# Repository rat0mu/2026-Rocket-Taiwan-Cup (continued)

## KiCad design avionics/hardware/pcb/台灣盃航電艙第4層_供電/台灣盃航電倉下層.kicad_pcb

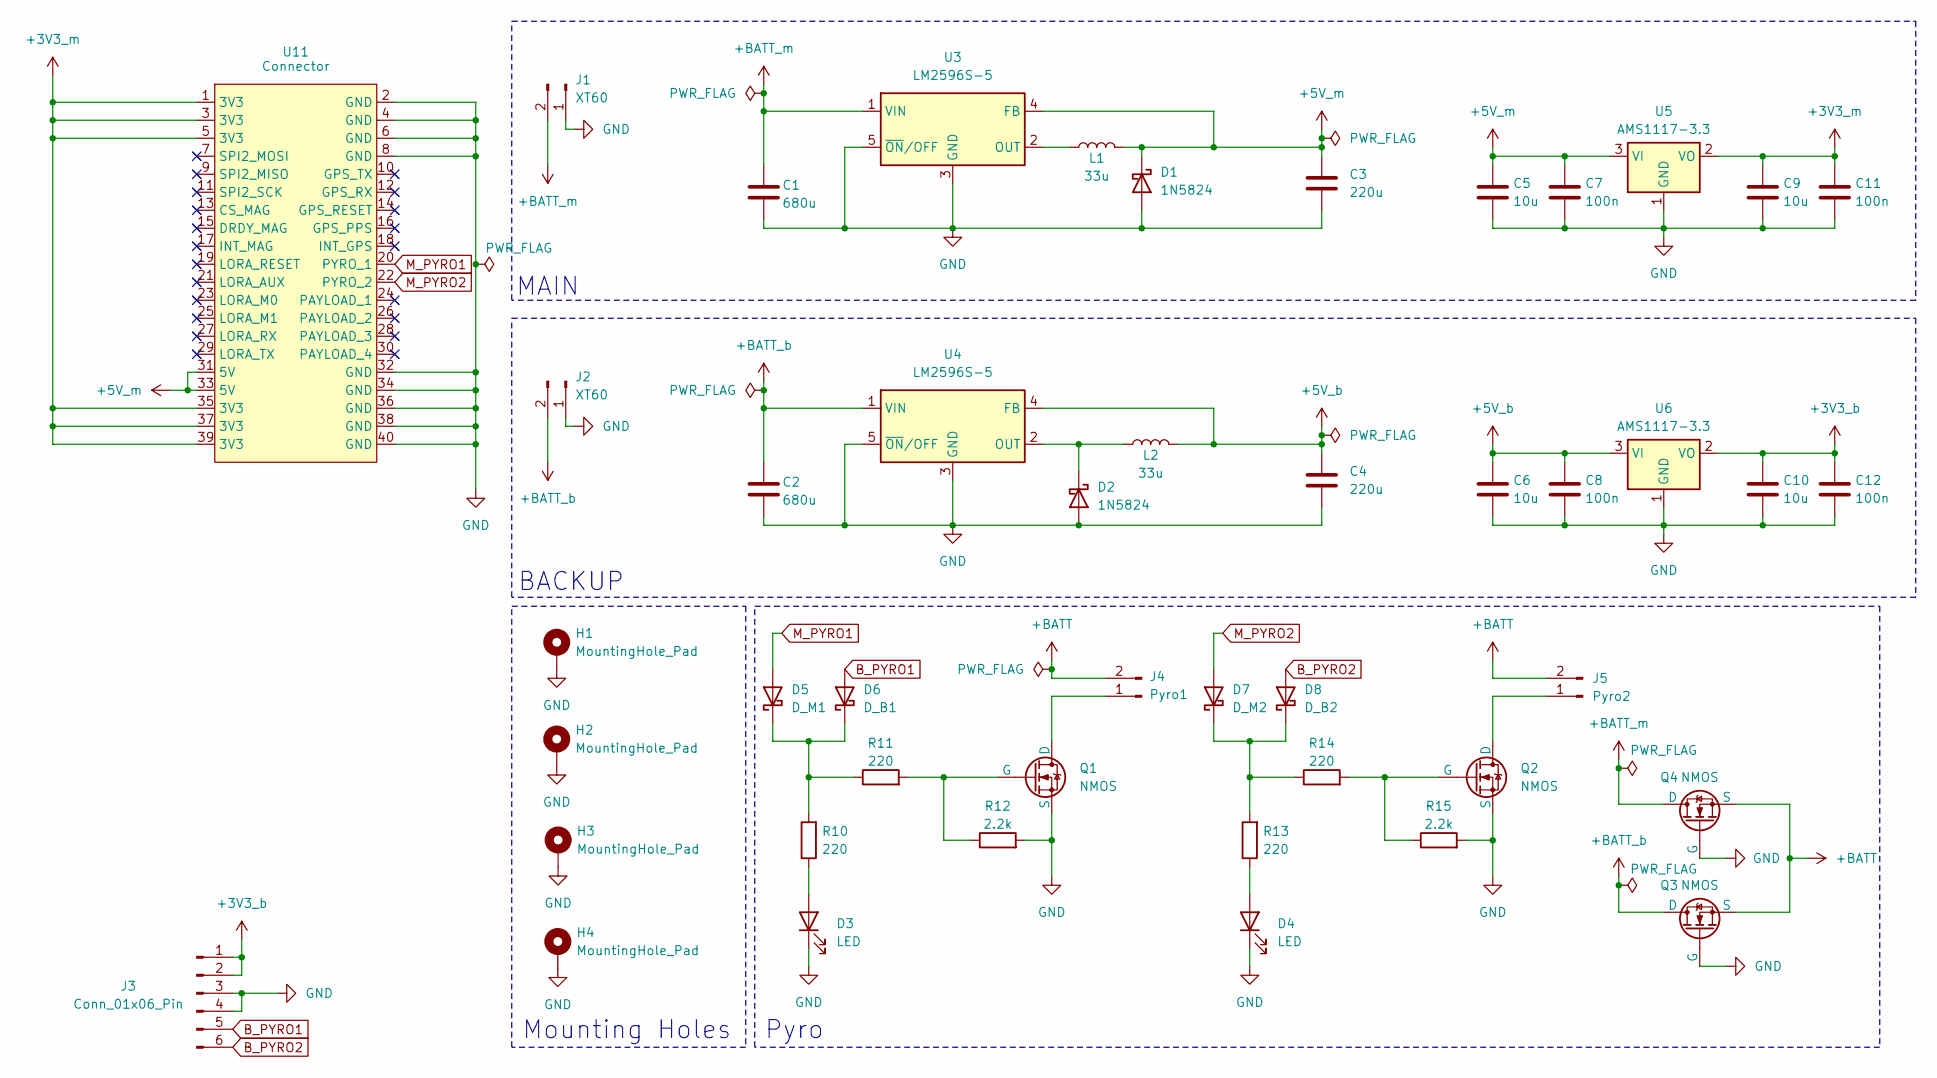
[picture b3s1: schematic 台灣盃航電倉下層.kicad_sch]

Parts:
C1, C2: 680u; CP_Elec_10x10
C3, C4: 220u; CP_Elec_8x10
C5, C6, C9, C10: 10u; C_0805_2012Metric
C7, C8, C11, C12: 100n; C_0603_1608Metric
D1, D2: 1N5824; D_SMC
D3, D4: LED; LED_0805_2012Metric
D5: D_M1; D_SOD-123
D6: D_B1; D_SOD-123
D7: D_M2; D_SOD-123
D8: D_B2; D_SOD-123
H1, H2, H3, H4: MountingHole_Pad; MountingHole_3.2mm_M3_ISO14580_Pad
J1, J2: XT60; AMASS_XT60PW-M_1x02_P7.20mm_Horizontal
J3: Conn_01x06_Pin; JST_XH_S6B-XH-A_1x06_P2.50mm_Horizontal
J4: Pyro1; JST_XH_S2B-XH-A_1x02_P2.50mm_Horizontal
J5: Pyro2; JST_XH_S2B-XH-A_1x02_P2.50mm_Horizontal
L1, L2: 33u; L_APV_ANR6045
Q1, Q2, Q3, Q4: NMOS; SOT-223
R10, R11, R13, R14: 220; R_0805_2012Metric
R12, R15: 2.2k; R_0805_2012Metric
U3, U4: LM2596S-5; TO-263-5_TabPin3
U5, U6: AMS1117-3.3; SOT-223-3_TabPin2
U11: Connector; PinHeader_2x20_P2.54mm_Vertical

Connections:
+3V3_b: C10.1, C12.1, J3.1, J3.2, U6.2 (VO)
+3V3_m: C9.1, C11.1, U5.2 (VO), U11.1 (3V3), U11.3 (3V3), U11.5 (3V3), U11.35 (3V3), U11.37 (3V3), U11.39 (3V3)
+5V_b: C4.1, C6.1, C8.1, L2.2, U4.4 (FB), U6.3 (VI)
+5V_m: C3.1, C5.1, C7.1, D1.1 (K), L1.2, U3.4 (FB), U5.3 (VI), U11.31 (5V), U11.33 (5V)
+BATT: J4.2, J5.2, Q3.3 (S), Q4.3 (S); also elsewhere on the board
+BATT_b: C2.1, J2.2, Q3.1 (D), U4.1 (VIN)
+BATT_m: C1.1, J1.2, Q4.1 (D), U3.1 (VIN)
B_PYRO1: D6.2 (A), J3.5
B_PYRO2: D8.2 (A), J3.6
GND: C1.2, C2.2, C3.2, C4.2, C5.2, C6.2, C7.2, C8.2, C9.2, C10.2, C11.2, C12.2, D1.2 (A), D2.2 (A), D3.1 (K), D4.1 (K), H1.1, H2.1, H3.1, H4.1, J1.1, J2.1, J3.3, J3.4, Q1.3 (S), Q2.3 (S), Q3.2 (G), Q4.2 (G), R12.2, R15.2, U3.3 (GND), U3.5 (~ON/OFF), U4.3 (GND), U4.5 (~ON/OFF), U5.1 (GND), U6.1 (GND), U11.2 (GND), U11.4 (GND), U11.6 (GND), U11.8 (GND), U11.32 (GND), U11.34 (GND), U11.36 (GND), U11.38 (GND), U11.40 (GND)
M_PYRO1: D5.2 (A), U11.20 (PYRO_1)
M_PYRO2: D7.2 (A), U11.22 (PYRO_2)
unnamed: D2.1 (K), L2.1, U4.2 (OUT)
unnamed: D3.2 (A), R10.1
unnamed: D4.2 (A), R13.1
unnamed: D5.1 (K), D6.1 (K), R10.2, R11.1
unnamed: D7.1 (K), D8.1 (K), R13.2, R14.1
unnamed 17: J4.1, Q1.1 (D); also elsewhere on the board
unnamed 18: J5.1, Q2.1 (D); also elsewhere on the board
unnamed: Q1.2 (G), R11.2, R12.1
unnamed: Q2.2 (G), R14.2, R15.1
unnamed: L1.1, U3.2 (OUT)

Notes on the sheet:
MAIN
Pyro
BACKUP
Mounting Holes

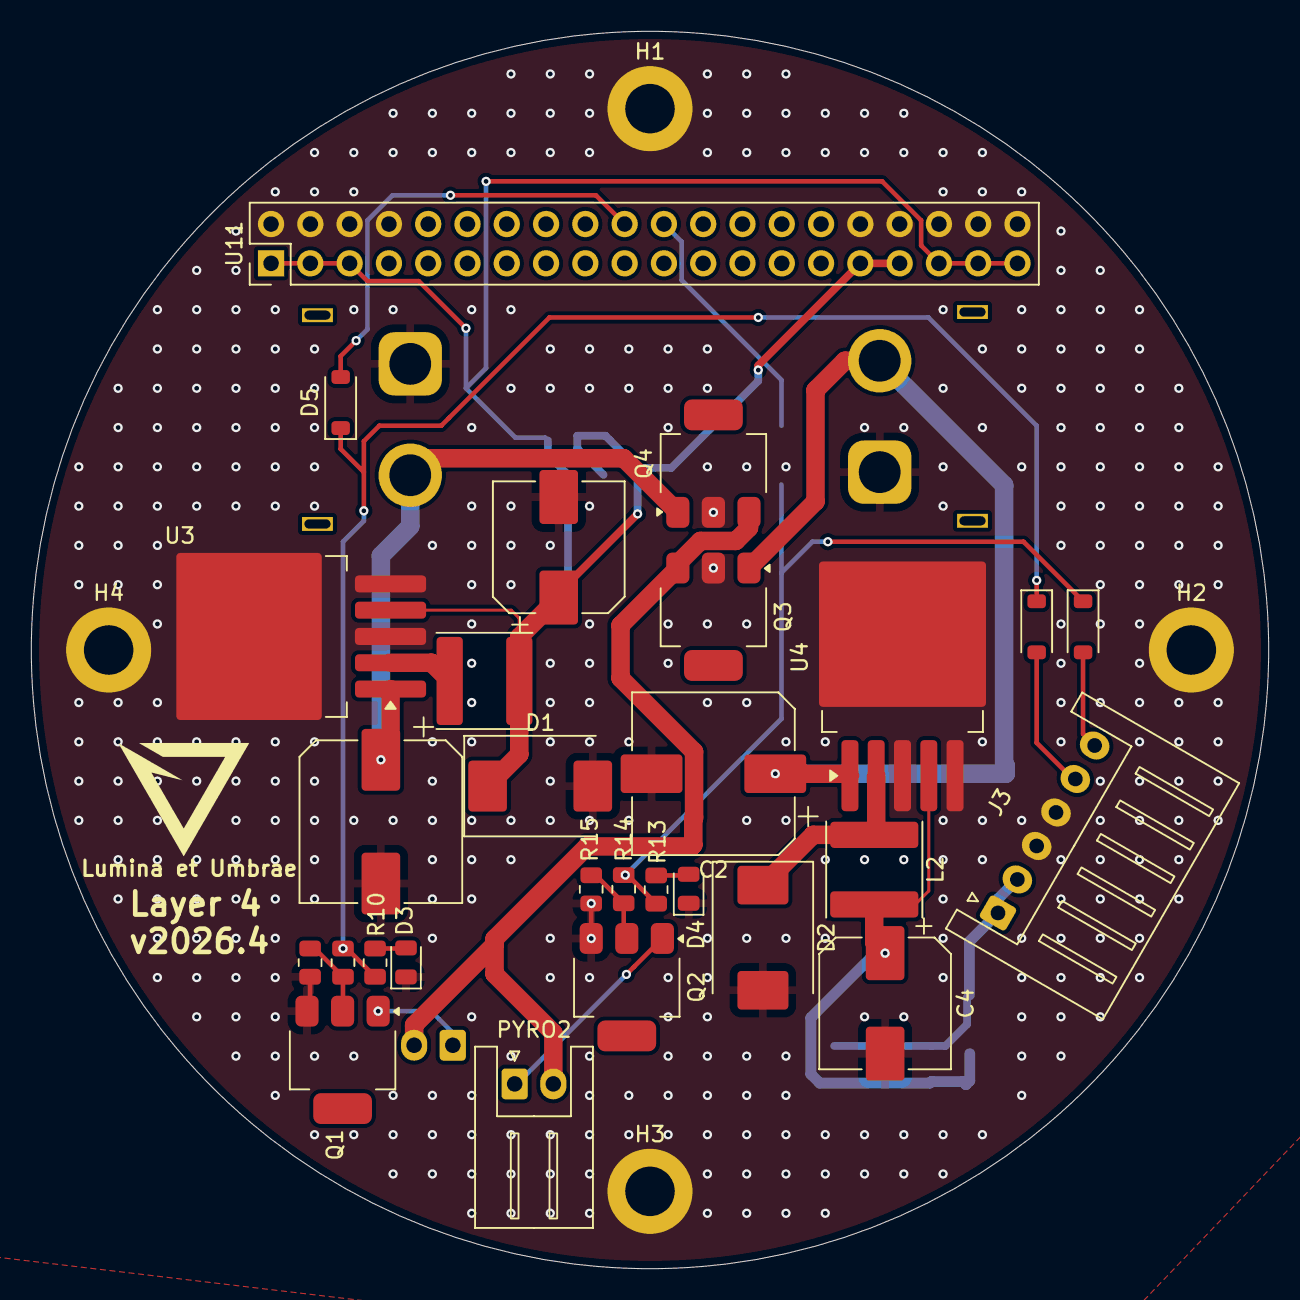
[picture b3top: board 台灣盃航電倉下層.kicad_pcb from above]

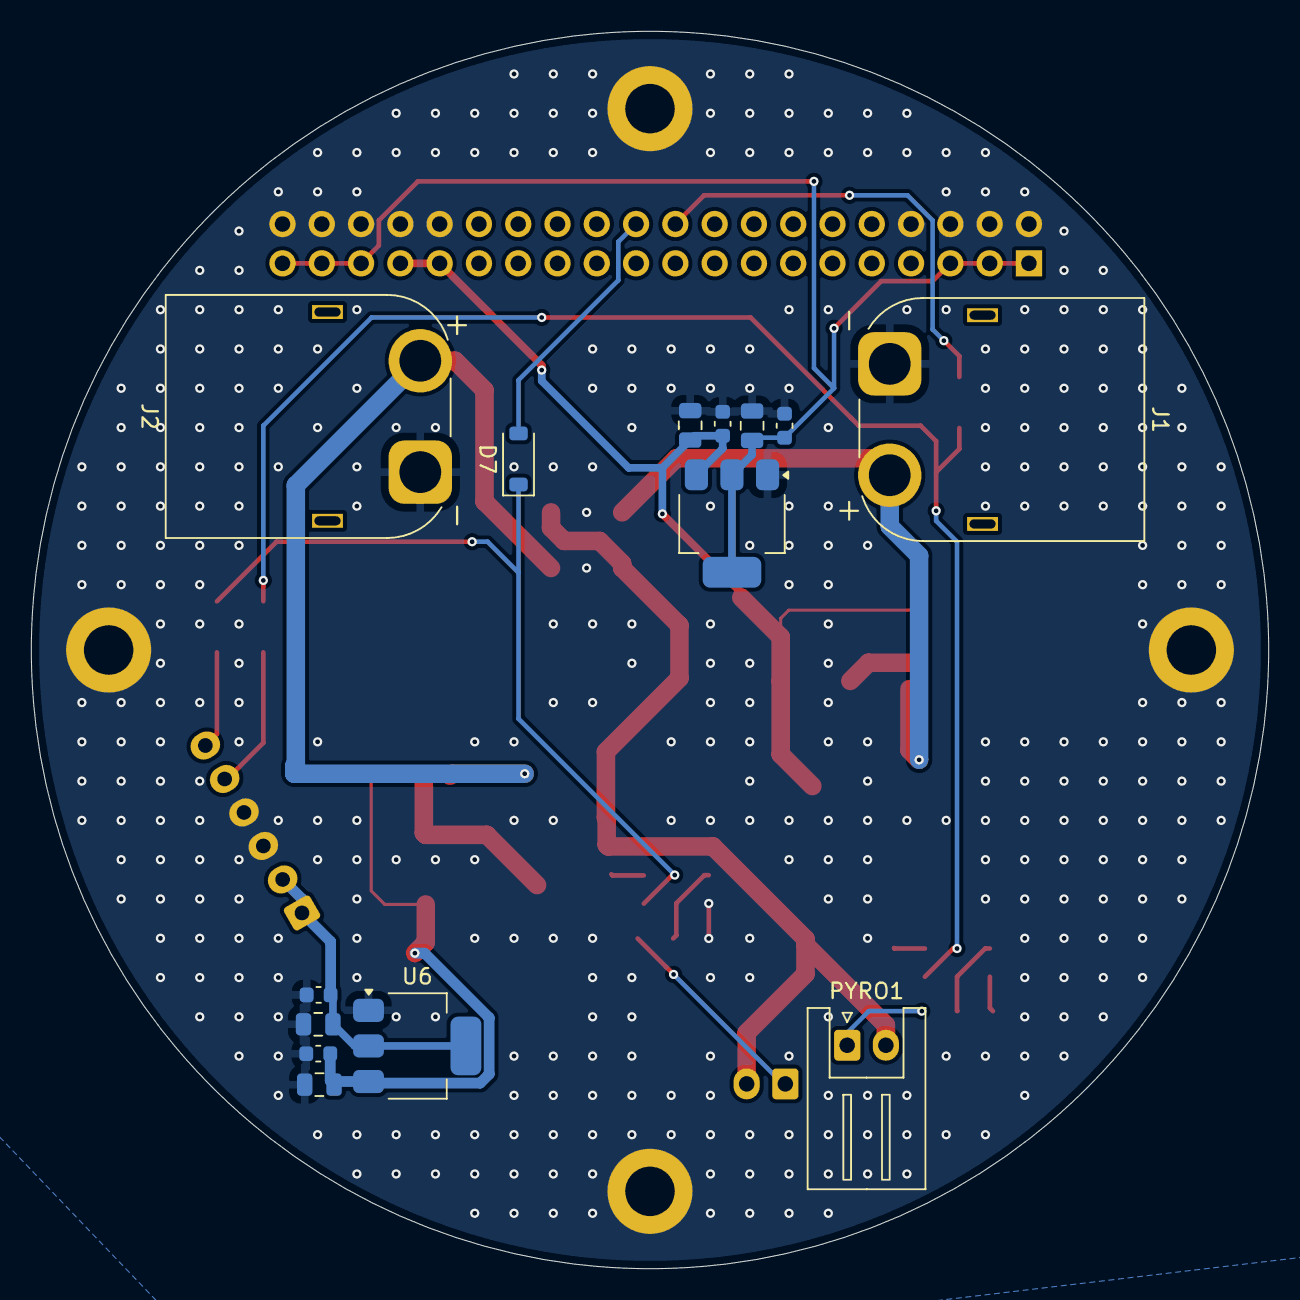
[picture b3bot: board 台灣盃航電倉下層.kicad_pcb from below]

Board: 2 copper layers, 80.0 x 80.0 mm, 46 parts (14 on the bottom side), 22 nets.

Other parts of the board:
PYRO1: Pyro1; JST_XH_S2B-XH-A_1x02_P2.50mm_Horizontal
PYRO2: Pyro2; JST_XH_S2B-XH-A_1x02_P2.50mm_Horizontal

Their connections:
+BATT: PYRO1.2, PYRO2.2; also elsewhere on the board
unnamed 17: PYRO1.1; also elsewhere on the board
unnamed 18: PYRO2.1; also elsewhere on the board

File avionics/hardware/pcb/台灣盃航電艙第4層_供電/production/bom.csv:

Designator,Footprint,Quantity,Value,LCSC Part #
"C1, C2",CP_Elec_10x10,2,680u,
"C10, C5, C6, C9",0805,4,10u,
"C11, C12, C7, C8",0603,4,100n,
"C3, C4",CP_Elec_8x10,2,220u,
"D1, D2",D_SMC,2,1N5824,
"D3, D4",0805,2,LED,
D5,D_SOD-123,1,D_M1,
D6,D_SOD-123,1,D_B1,
D7,D_SOD-123,1,D_M2,
D8,D_SOD-123,1,D_B2,
"J1, J2",AMASS_XT60PW-M_1x02_P7.20mm_Horizontal,2,XT60,
J3,JST_XH_S6B-XH-A_1x06_P2.50mm_Horizontal,1,Conn_01x06_Pin,
"L1, L2",L_APV_ANR6045,2,33u,
PYRO1,JST_XH_S2B-XH-A_1x02_P2.50mm_Horizontal,1,Pyro1,
PYRO2,JST_XH_S2B-XH-A_1x02_P2.50mm_Horizontal,1,Pyro2,
"Q1, Q2, Q3, Q4",SOT-223,4,NMOS,
"R10, R11, R13, R14",0805,4,220,
"R12, R15",0805,2,2.2k,
U11,PinHeader_2x20_P2.54mm_Vertical,1,Connector,
"U3, U4",TO-263-5_TabPin3,2,LM2596S-5,
"U5, U6",SOT-223-3_TabPin2,2,AMS1117-3.3,

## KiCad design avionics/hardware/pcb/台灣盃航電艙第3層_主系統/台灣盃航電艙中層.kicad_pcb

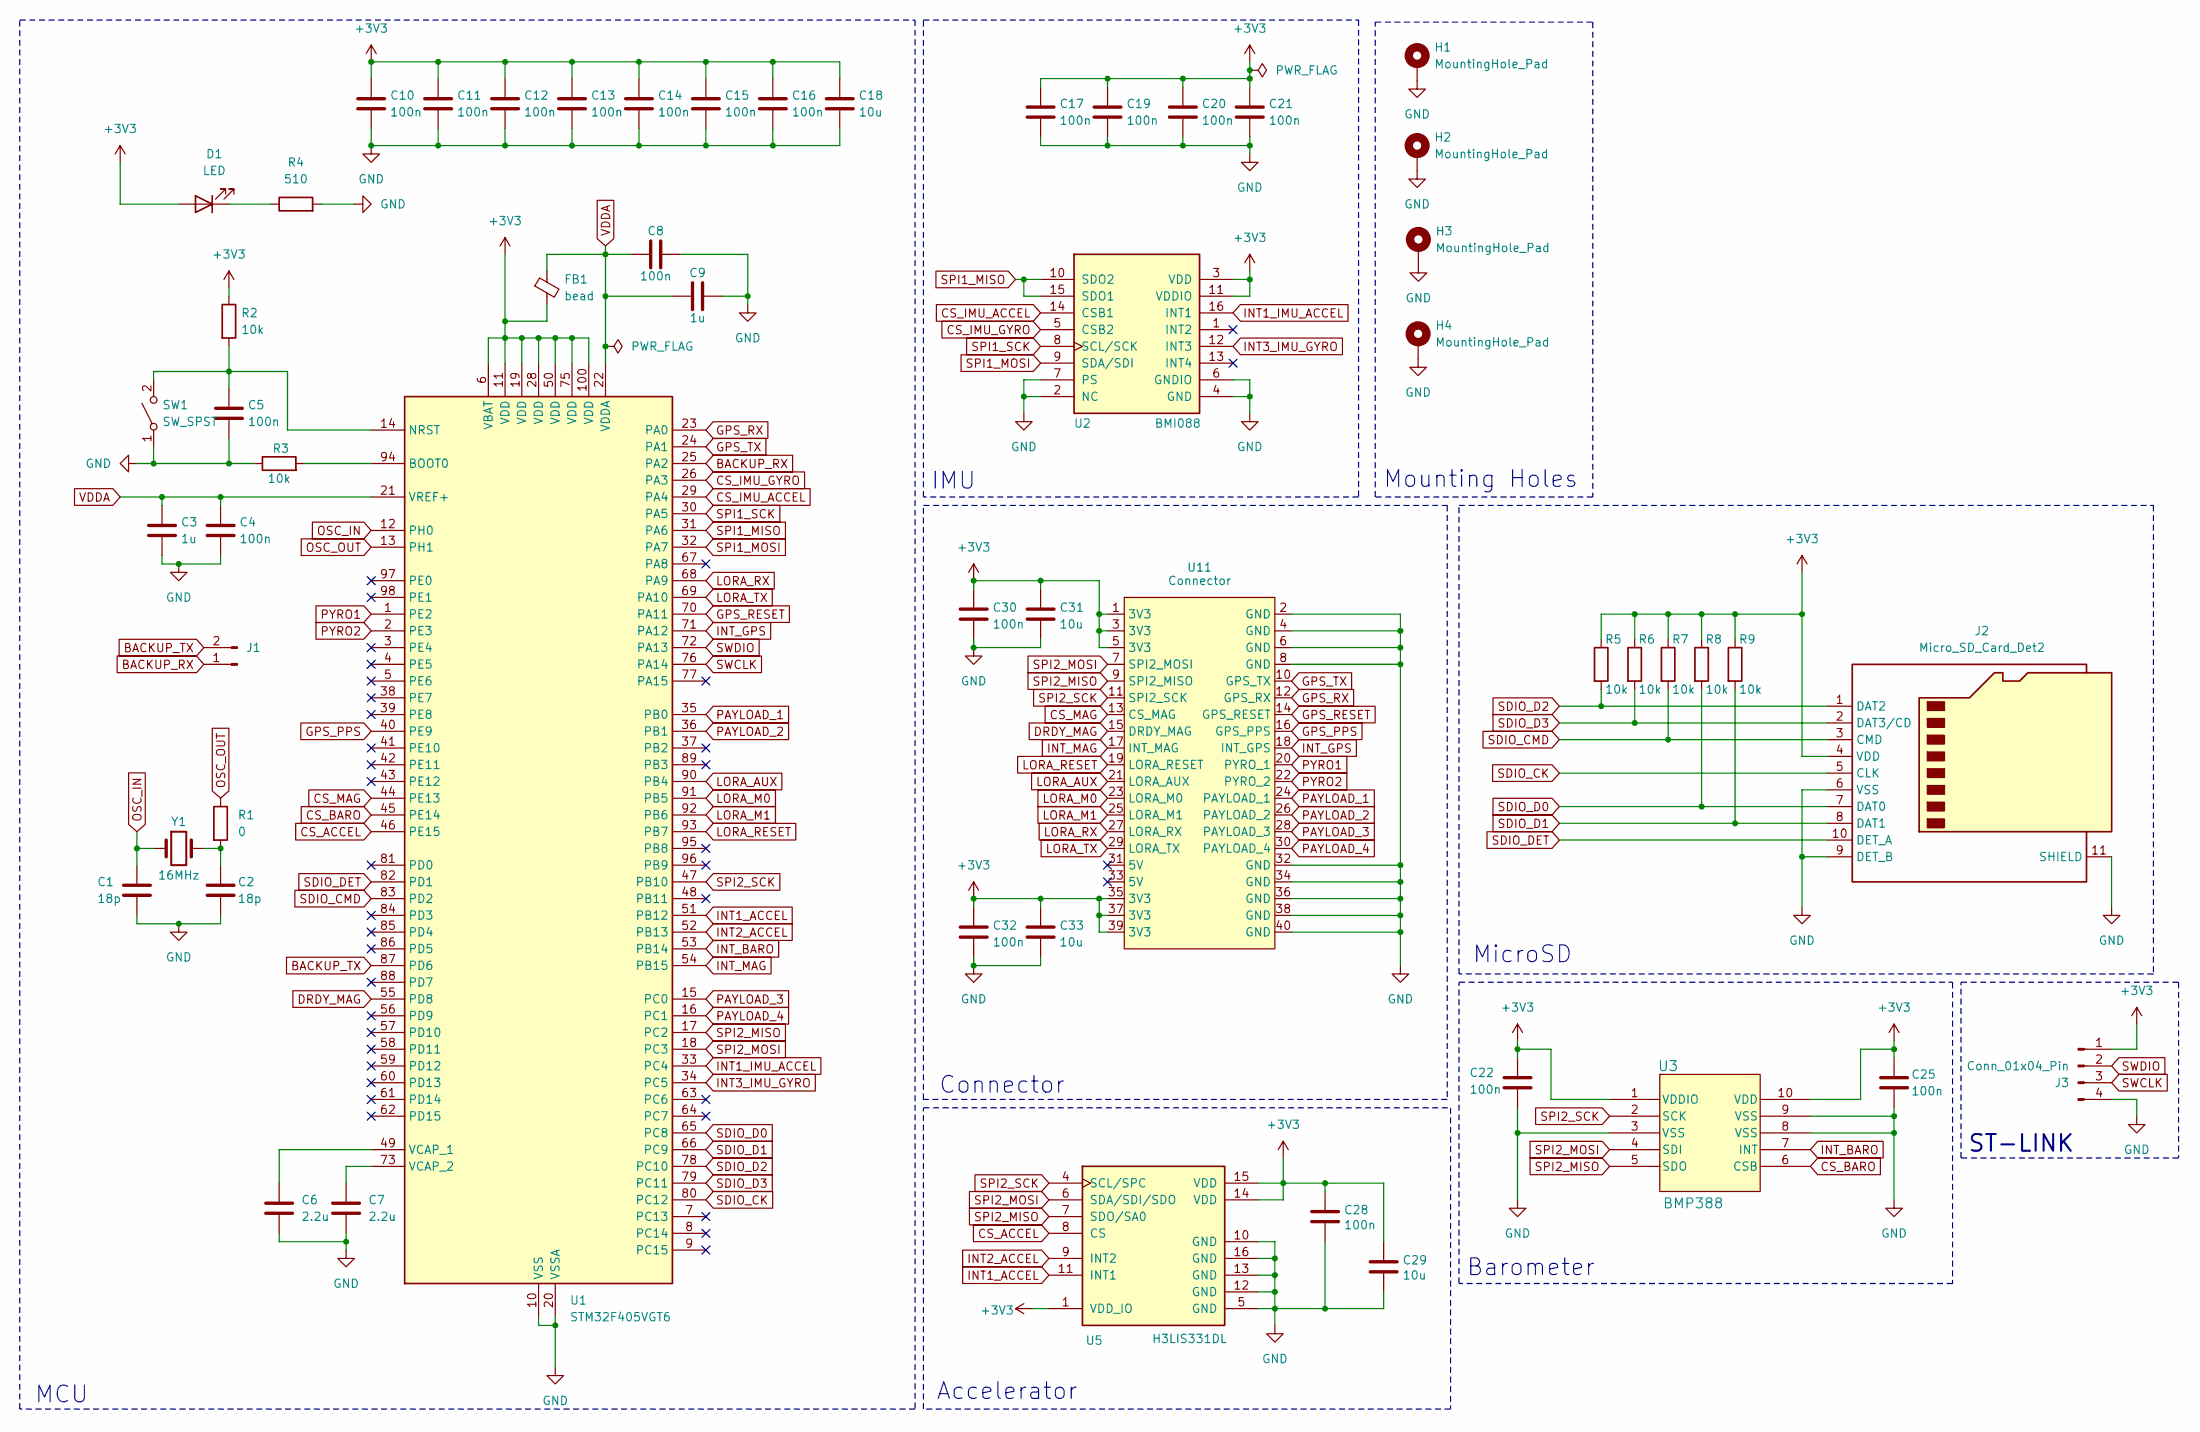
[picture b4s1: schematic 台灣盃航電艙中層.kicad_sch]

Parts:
C1, C2: 18p; C_0603_1608Metric
C3, C9: 1u; C_0603_1608Metric
C4, C5, C8, C10, C11, C12, C13, C14, C15, C16, C17, C19, C20, C21, C22, C25, C28: 100n; C_0603_1608Metric
C6, C7: 2.2u; C_0805_2012Metric
C18, C29: 10u; C_0805_2012Metric
C30, C32: 100n; C_0402_1005Metric
C31, C33: 10u; C_0603_1608Metric
D1: LED; LED_0805_2012Metric
FB1: bead; L_0603_1608Metric
H1, H2, H3, H4: MountingHole_Pad; MountingHole_3.2mm_M3_ISO14580_Pad
J1: JST_XH_S2B-XH-A_1x02_P2.50mm_Horizontal
J2: Micro_SD_Card_Det2; microSD_HC_Hirose_DM3D-SF
J3: Conn_01x04_Pin; PinHeader_1x04_P2.54mm_Horizontal
R1: 0; R_0603_1608Metric
R2, R5, R6, R7, R8, R9: 10k; R_0603_1608Metric
R3: 10k; C_0603_1608Metric
R4: 510; R_0805_2012Metric
SW1: SW_SPST; SW_SPST_FSMSM
U1: STM32F405VGT6; LQFP-100_14x14mm_P0.5mm
U2: BMI088; PQFN50P450X300X100-16N
U3: BMP388; XDCR_BMP390L
U5: H3LIS331DL; QFN300X300X100-16N
U11: Connector; PinHeader_2x20_P2.54mm_Vertical
Y1: 16MHz; Crystal_SMD_3225-4Pin_3.2x2.5mm

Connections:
+3V3: C10.1, C11.1, C12.1, C13.1, C14.1, C15.1, C16.1, C17.1, C18.1, C19.1, C20.1, C21.1, C22.1, C25.1, C28.1, C29.1, C30.1, C31.1, C32.1, C33.1, D1.2 (A), FB1.2, J2.4 (VDD), J3.1, R2.1, R5.1, R6.1, R7.1, R8.1, R9.1, U1.6 (VBAT), U1.11 (VDD), U1.19 (VDD), U1.28 (VDD), U1.50 (VDD), U1.75 (VDD), U1.100 (VDD), U2.3 (VDD), U2.11 (VDDIO), U3.1 (VDDIO), U3.10 (VDD), U5.1 (VDD_IO), U5.14 (VDD), U5.15 (VDD), U11.1 (3V3), U11.3 (3V3), U11.5 (3V3), U11.35 (3V3), U11.37 (3V3), U11.39 (3V3)
BACKUP_RX: J1.1, U1.25 (PA2)
BACKUP_TX: J1.2, U1.87 (PD6)
CS_ACCEL: U1.46 (PE15), U5.8 (CS)
CS_BARO: U1.45 (PE14), U3.6 (CSB)
CS_IMU_ACCEL: U1.29 (PA4), U2.14 (CSB1)
CS_IMU_GYRO: U1.26 (PA3), U2.5 (CSB2)
CS_MAG: U1.44 (PE13), U11.13 (CS_MAG)
DRDY_MAG: U1.55 (PD8), U11.15 (DRDY_MAG)
GND: C1.2, C2.2, C3.2, C4.2, C5.2, C6.2, C7.2, C8.1, C9.2, C10.2, C11.2, C12.2, C13.2, C14.2, C15.2, C16.2, C17.2, C18.2, C19.2, C20.2, C21.2, C22.2, C25.2, C28.2, C29.2, C30.2, C31.2, C32.2, C33.2, H1.1, H2.1, H3.1, H4.1, J2.6 (VSS), J2.9 (DET_B), J2.11 (SHIELD), J3.4, R3.1, R4.2, SW1.1 (A), U1.10 (VSS), U1.20 (VSSA), U1.27 (VSS), U1.74 (VSS), U1.99 (VSS), U2.2 (NC), U2.4 (GND), U2.6 (GNDIO), U2.7 (PS), U3.3 (VSS), U3.8 (VSS), U3.9 (VSS), U5.5 (GND), U5.10 (GND), U5.12 (GND), U5.13 (GND), U5.16 (GND), U11.2 (GND), U11.4 (GND), U11.6 (GND), U11.8 (GND), U11.32 (GND), U11.34 (GND), U11.36 (GND), U11.38 (GND), U11.40 (GND)
GPS_PPS: U1.40 (PE9), U11.16 (GPS_PPS)
GPS_RESET: U1.70 (PA11), U11.14 (GPS_RESET)
GPS_RX: U1.23 (PA0), U11.12 (GPS_RX)
GPS_TX: U1.24 (PA1), U11.10 (GPS_TX)
INT1_ACCEL: U1.51 (PB12), U5.11 (INT1)
INT1_IMU_ACCEL: U1.33 (PC4), U2.16 (INT1)
INT2_ACCEL: U1.52 (PB13), U5.9 (INT2)
INT3_IMU_GYRO: U1.34 (PC5), U2.12 (INT3)
INT_BARO: U1.53 (PB14), U3.7 (INT)
INT_GPS: U1.71 (PA12), U11.18 (INT_GPS)
INT_MAG: U1.54 (PB15), U11.17 (INT_MAG)
LORA_AUX: U1.90 (PB4), U11.21 (LORA_AUX)
LORA_M0: U1.91 (PB5), U11.23 (LORA_M0)
LORA_M1: U1.92 (PB6), U11.25 (LORA_M1)
LORA_RESET: U1.93 (PB7), U11.19 (LORA_RESET)
LORA_RX: U1.68 (PA9), U11.27 (LORA_RX)
LORA_TX: U1.69 (PA10), U11.29 (LORA_TX)
unnamed: C2.1, R1.2, Y1.2
unnamed: D1.1 (K), R4.1
unnamed: C5.1, R2.2, SW1.2 (B), U1.14 (NRST)
unnamed: R3.2, U1.94 (BOOT0)
unnamed: C6.1, U1.49 (VCAP_1)
unnamed: C7.1, U1.73 (VCAP_2)
OSC_IN: C1.1, U1.12 (PH0), Y1.1
OSC_OUT: R1.1, U1.13 (PH1)
PAYLOAD_1: U1.35 (PB0), U11.24 (PAYLOAD_1)
PAYLOAD_2: U1.36 (PB1), U11.26 (PAYLOAD_2)
PAYLOAD_3: U1.15 (PC0), U11.28 (PAYLOAD_3)
PAYLOAD_4: U1.16 (PC1), U11.30 (PAYLOAD_4)
PYRO1: U1.1 (PE2), U11.20 (PYRO_1)
PYRO2: U1.2 (PE3), U11.22 (PYRO_2)
SDIO_CK: J2.5 (CLK), U1.80 (PC12)
SDIO_CMD: J2.3 (CMD), R7.2, U1.83 (PD2)
SDIO_D0: J2.7 (DAT0), R8.2, U1.65 (PC8)
SDIO_D1: J2.8 (DAT1), R9.2, U1.66 (PC9)
SDIO_D2: J2.1 (DAT2), R5.2, U1.78 (PC10)
SDIO_D3: J2.2 (DAT3/CD), R6.2, U1.79 (PC11)
SDIO_DET: J2.10 (DET_A), U1.82 (PD1)
SPI1_MISO: U1.31 (PA6), U2.10 (SDO2), U2.15 (SDO1)
SPI1_MOSI: U1.32 (PA7), U2.9 (SDA/SDI)
SPI1_SCK: U1.30 (PA5), U2.8 (SCL/SCK)
SPI2_MISO: U1.17 (PC2), U3.5 (SDO), U5.7 (SDO/SA0), U11.9 (SPI2_MISO)
SPI2_MOSI: U1.18 (PC3), U3.4 (SDI), U5.6 (SDA/SDI/SDO), U11.7 (SPI2_MOSI)
SPI2_SCK: U1.47 (PB10), U3.2 (SCK), U5.4 (SCL/SPC), U11.11 (SPI2_SCK)
SWCLK: J3.3, U1.76 (PA14)
SWDIO: J3.2, U1.72 (PA13)
VDDA: C3.1, C4.1, C8.2, C9.1, FB1.1, U1.21 (VREF+), U1.22 (VDDA)

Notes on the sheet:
IMU
MCU
Mounting Holes
Accelerator
MicroSD
Connector
ST-LINK
Barometer

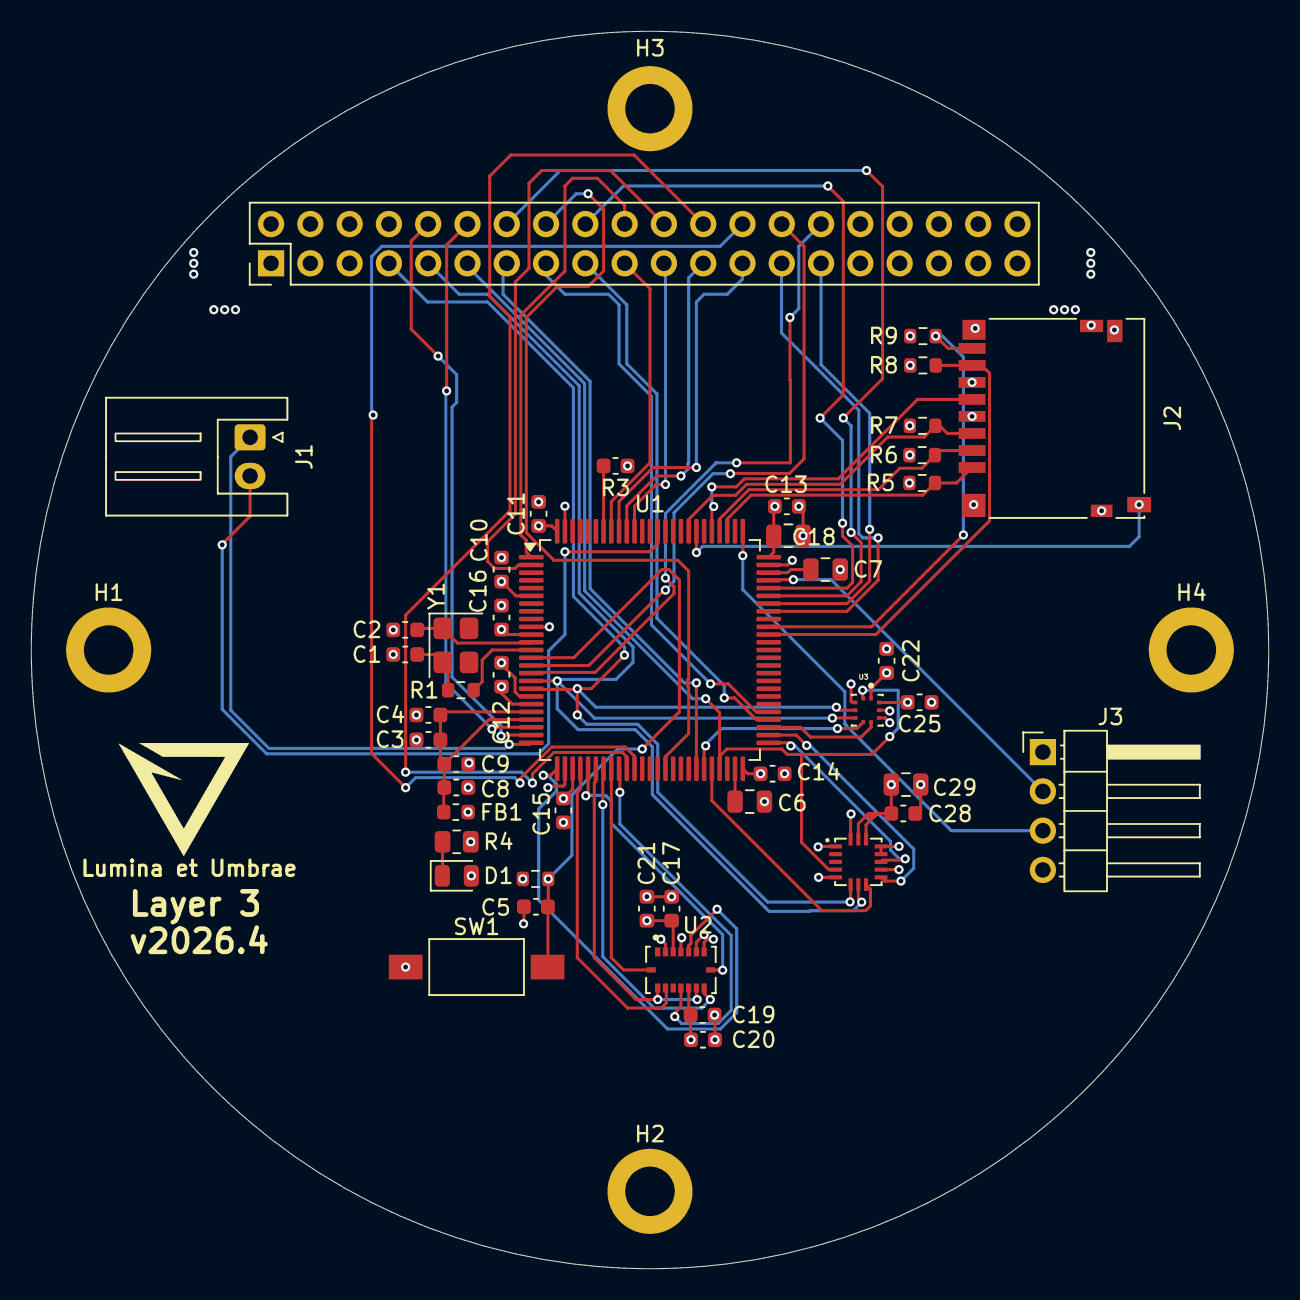
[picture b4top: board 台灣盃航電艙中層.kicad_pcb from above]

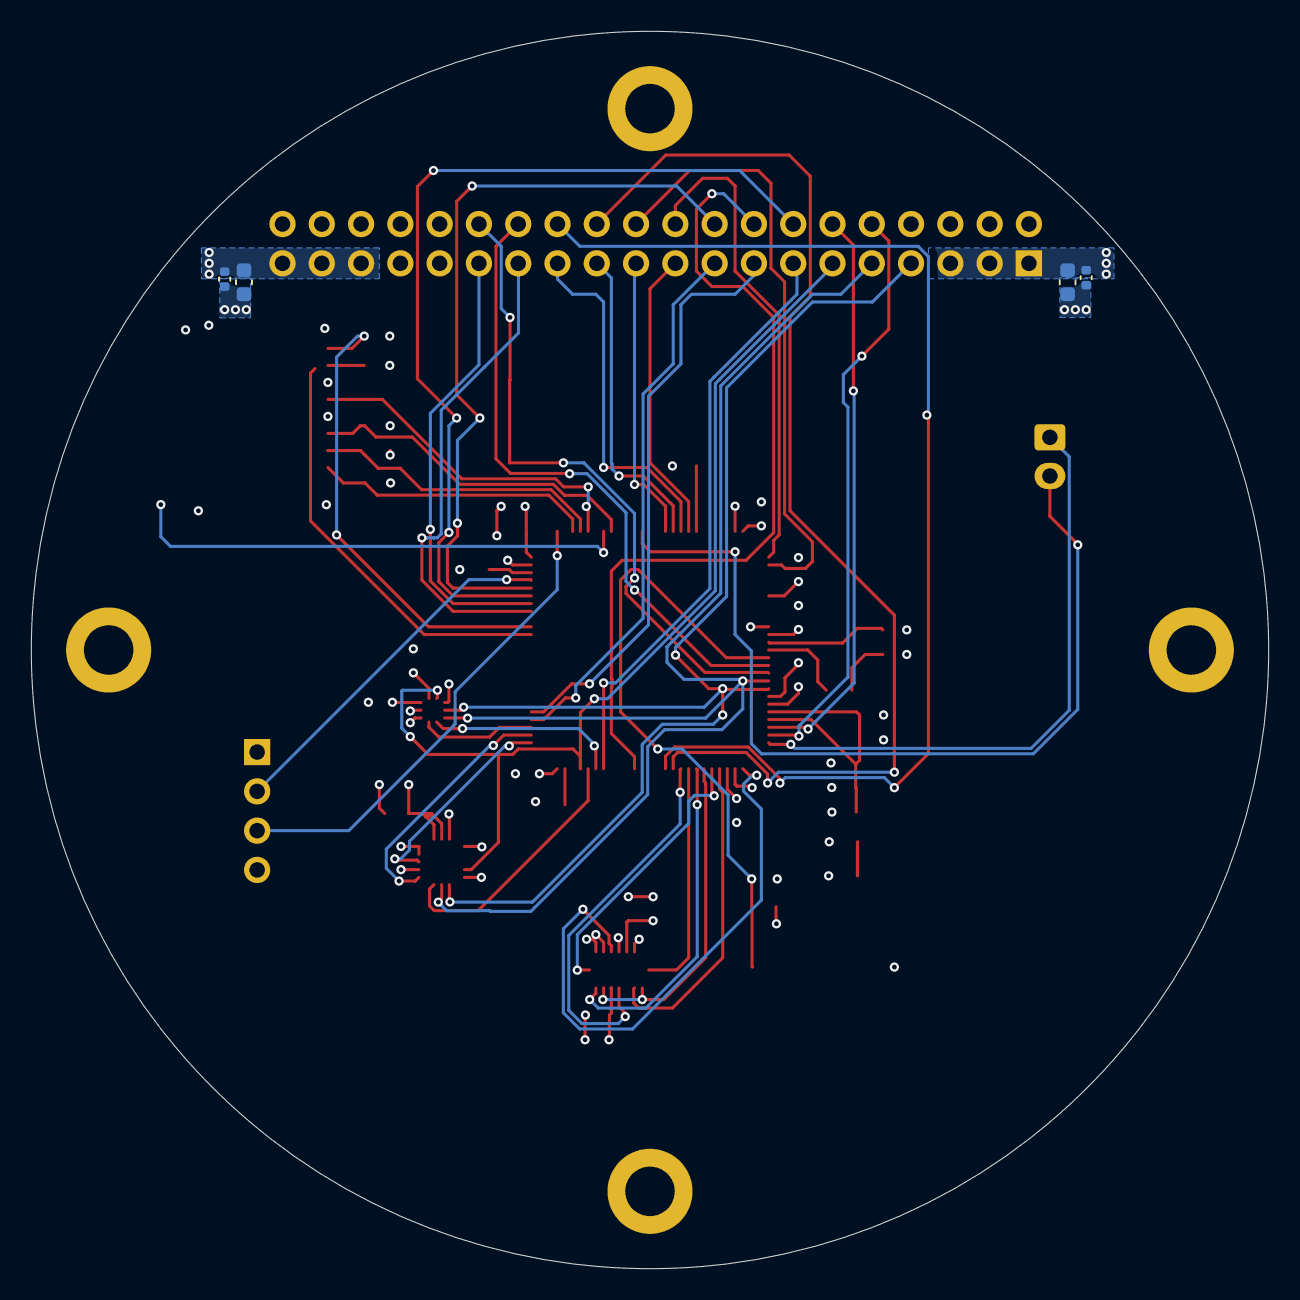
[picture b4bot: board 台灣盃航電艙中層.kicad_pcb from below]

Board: 4 copper layers, 80.0 x 80.0 mm, 54 parts (4 on the bottom side), 57 nets.

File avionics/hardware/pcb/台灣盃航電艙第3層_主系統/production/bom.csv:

Designator,Footprint,Quantity,Value,LCSC Part #
"C1, C2",0603,2,18p,
"C10, C11, C12, C13, C14, C15, C16, C17, C19, C20, C21, C22, C25, C28, C4, C5, C8",0603,17,100n,
"C18, C29",0805,2,10u,
"C3, C9",0603,2,1u,
"C30, C32",0402,2,100n,
"C31, C33",0603,2,10u,
"C6, C7",0805,2,2.2u,
D1,0805,1,LED,
FB1,0603,1,bead,
J1,JST_XH_S2B-XH-A_1x02_P2.50mm_Horizontal,1,~,
J2,microSD_HC_Hirose_DM3D-SF,1,Micro_SD_Card_Det2,
J3,PinHeader_1x04_P2.54mm_Horizontal,1,Conn_01x04_Pin,
R1,0603,1,0,
"R2, R3, R5, R6, R7, R8, R9",0603,7,10k,
R4,0805,1,510,
SW1,SW_SPST_FSMSM,1,SW_SPST,
U1,LQFP-100_14x14mm_P0.5mm,1,STM32F405VGT6,
U11,PinHeader_2x20_P2.54mm_Vertical,1,Connector,
U2,PQFN50P450X300X100-16N,1,BMI088,
U3,XDCR_BMP390L,1,BMP388,
U5,QFN300X300X100-16N,1,H3LIS331DL,
Y1,Crystal_SMD_3225-4Pin_3.2x2.5mm,1,16MHz,

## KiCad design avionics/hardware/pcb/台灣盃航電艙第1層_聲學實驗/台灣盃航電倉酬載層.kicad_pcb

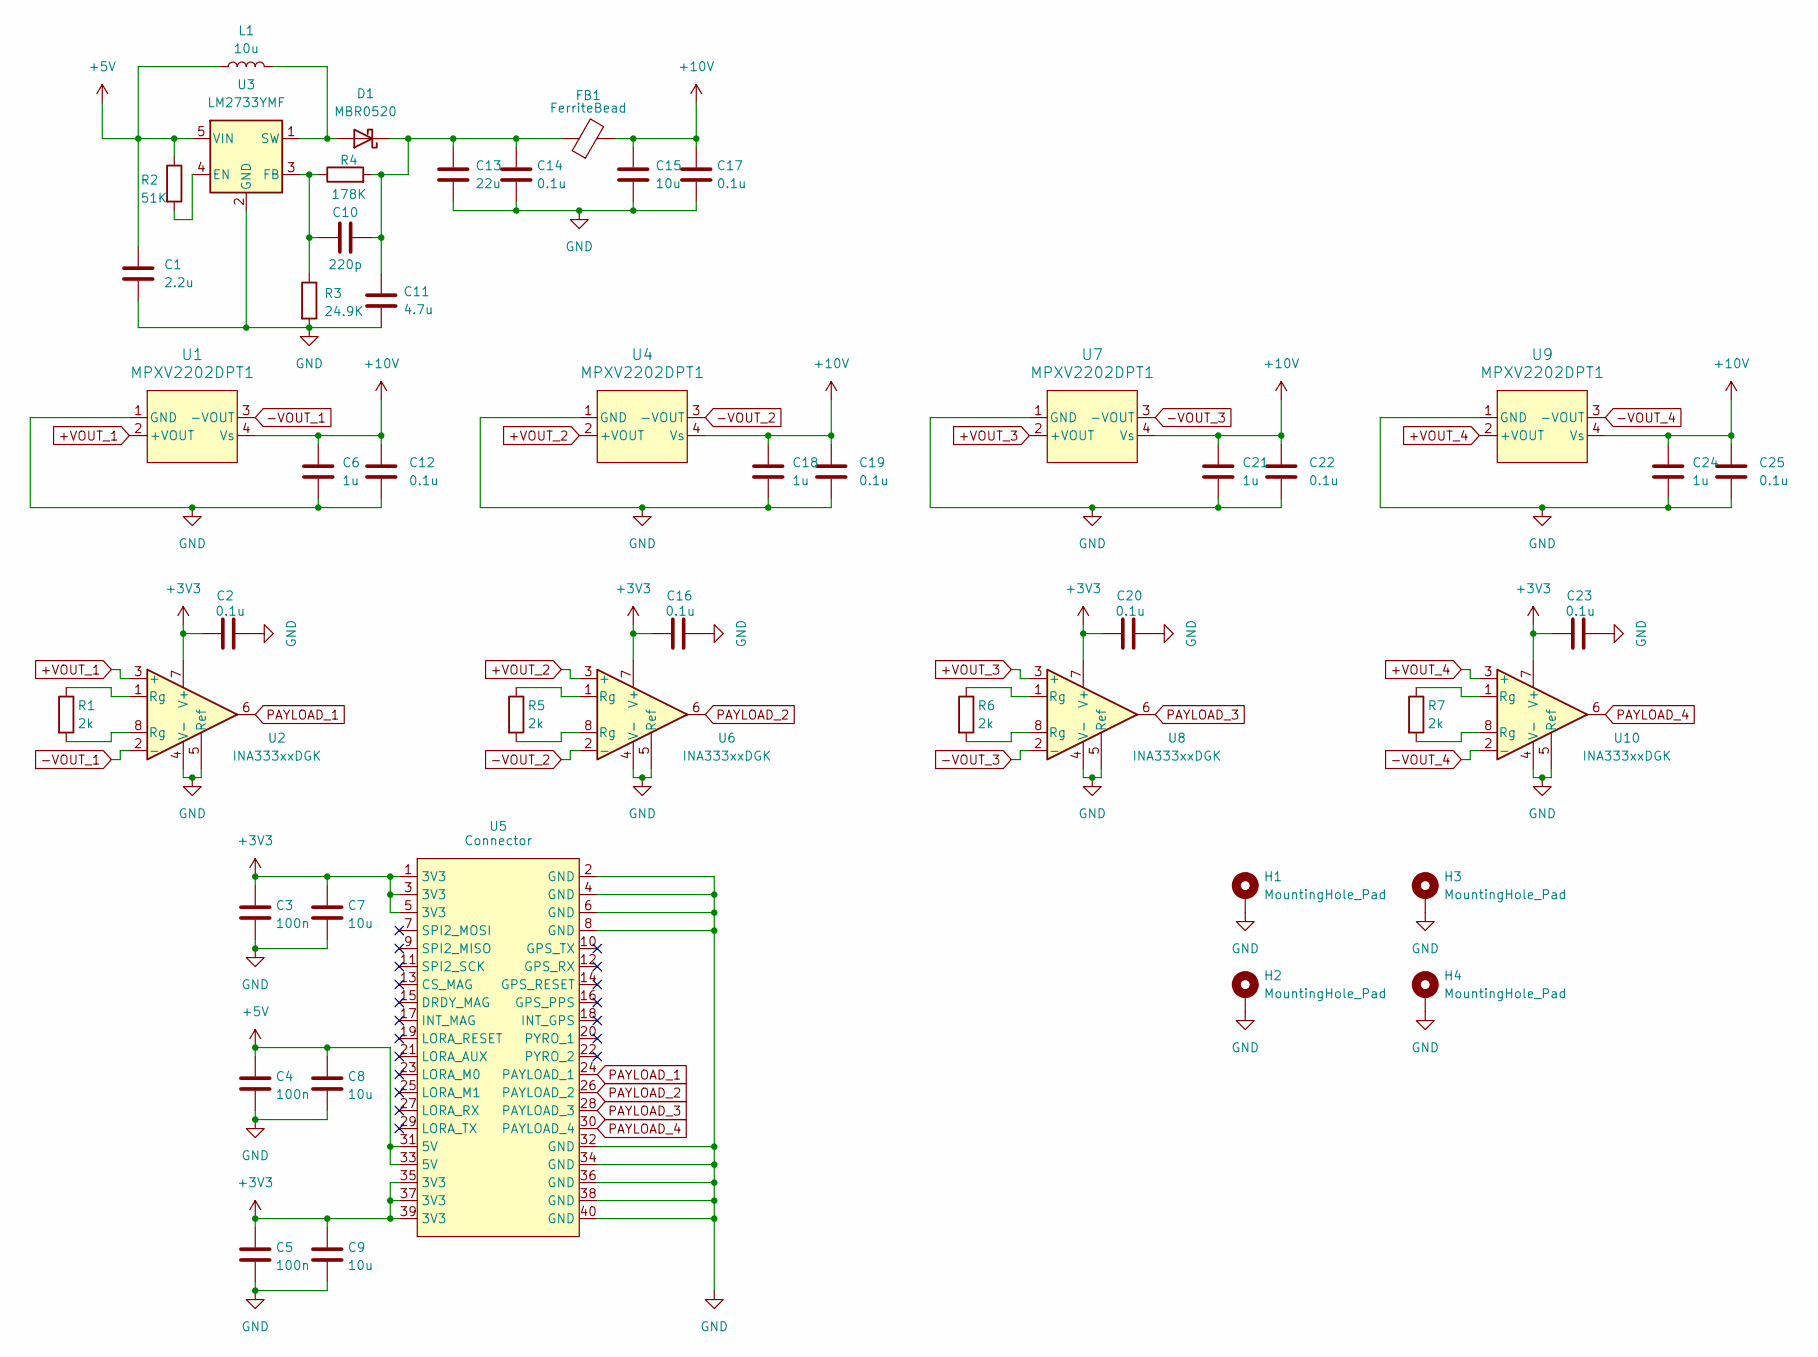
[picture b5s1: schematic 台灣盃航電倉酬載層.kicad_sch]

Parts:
C1: 2.2u; C_0603_1608Metric
C2, C12, C14, C16, C17, C19, C20, C22, C23, C25: 0.1u; C_0402_1005Metric
C3, C4, C5: 100n; C_0402_1005Metric
C6, C18, C21, C24: 1u; C_0402_1005Metric
C7, C8, C9, C15: 10u; C_0603_1608Metric
C10: 220p; C_0402_1005Metric
C11: 4.7u; C_0603_1608Metric
C13: 22u; C_0805_2012Metric
D1: MBR0520; D_SOD-123
FB1: FerriteBead; L_0603_1608Metric
H1, H2, H3, H4: MountingHole_Pad; MountingHole_2.2mm_M2_DIN965_Pad
L1: 10u; L_1206_3216Metric
R1, R5, R6, R7: 2k; R_0603_1608Metric
R2: 51K; R_0603_1608Metric
R3: 24.9K; R_0603_1608Metric
R4: 178K; R_0603_1608Metric
U1, U4, U7, U9: MPXV2202DPT1; XDCR_MPXV2202DPT1
U2, U6, U8, U10: INA333xxDGK; VSSOP-8_3x3mm_P0.65mm
U3: LM2733YMF; SOT-23-5
U5: Connector; PinHeader_2x20_P2.54mm_Vertical

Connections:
+3V3: C2.1, C3.1, C5.1, C7.1, C9.1, C16.1, C20.1, C23.1, U2.7 (V+), U5.1 (3V3), U5.3 (3V3), U5.5 (3V3), U5.35 (3V3), U5.37 (3V3), U5.39 (3V3), U6.7 (V+), U8.7 (V+), U10.7 (V+)
+5V: C1.1, C4.1, C8.1, L1.1, R2.1, U3.5 (VIN), U5.31 (5V), U5.33 (5V)
+10V: C6.1, C12.1, C15.1, C17.1, C18.1, C19.1, C21.1, C22.1, C24.1, C25.1, FB1.2, U1.4 (Vs), U4.4 (Vs), U7.4 (Vs), U9.4 (Vs)
+VOUT_1: U1.2 (+VOUT), U2.3 (+)
+VOUT_2: U4.2 (+VOUT), U6.3 (+)
+VOUT_3: U7.2 (+VOUT), U8.3 (+)
+VOUT_4: U9.2 (+VOUT), U10.3 (+)
-VOUT_1: U1.3 (-VOUT), U2.2 (-)
-VOUT_2: U4.3 (-VOUT), U6.2 (-)
-VOUT_3: U7.3 (-VOUT), U8.2 (-)
-VOUT_4: U9.3 (-VOUT), U10.2 (-)
GND: C1.2, C2.2, C3.2, C4.2, C5.2, C6.2, C7.2, C8.2, C9.2, C11.2, C12.2, C13.2, C14.2, C15.2, C16.2, C17.2, C18.2, C19.2, C20.2, C21.2, C22.2, C23.2, C24.2, C25.2, H1.1, H2.1, H3.1, H4.1, R3.2, U1.1 (GND), U2.4 (V-), U2.5 (Ref), U3.2 (GND), U4.1 (GND), U5.2 (GND), U5.4 (GND), U5.6 (GND), U5.8 (GND), U5.32 (GND), U5.34 (GND), U5.36 (GND), U5.38 (GND), U5.40 (GND), U6.4 (V-), U6.5 (Ref), U7.1 (GND), U8.4 (V-), U8.5 (Ref), U9.1 (GND), U10.4 (V-), U10.5 (Ref)
unnamed: D1.2 (A), L1.2, U3.1 (SW)
unnamed: C10.2, C11.1, C13.1, C14.1, D1.1 (K), FB1.1, R4.2
unnamed: R1.1, U2.1 (Rg)
unnamed: R1.2, U2.8 (Rg)
unnamed: R5.1, U6.1 (Rg)
unnamed: R5.2, U6.8 (Rg)
unnamed: R6.1, U8.1 (Rg)
unnamed: R6.2, U8.8 (Rg)
unnamed: R7.1, U10.1 (Rg)
unnamed: R7.2, U10.8 (Rg)
unnamed: R2.2, U3.4 (EN)
unnamed: C10.1, R3.1, R4.1, U3.3 (FB)
PAYLOAD_1: U2.6, U5.24 (PAYLOAD_1)
PAYLOAD_2: U5.26 (PAYLOAD_2), U6.6
PAYLOAD_3: U5.28 (PAYLOAD_3), U8.6
PAYLOAD_4: U5.30 (PAYLOAD_4), U10.6
